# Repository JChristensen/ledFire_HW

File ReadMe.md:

# LED PWM Fire Effect (Hardware Design)#
http://github.com/JChristensen/ledFire_HW  
ReadMe file  
Jack Christensen Dec 2014

## Introduction ##

A small project to simulate the appearance of a candle or other small fire using pulse width modulation and an ATtiny84A microcontroller. The original application of this project was to light a Halloween jack-o-lantern.

[Here](https://vimeo.com/110424346) is a video.  
Firmware is available [on GitHub](http://goo.gl/VueLrD).  
PC boards can be ordered [from OSH Park](https://www.oshpark.com/shared_projects/ASV7G4qa).  
A Bill of Materials with Mouser part numbers is part of this repo.

## Circuit Details ##

The circuit is meant to run on two AA cells; either alkaline or rechargeable types (NiMH, NiCd) will work. Battery life with two fresh alkaline cells is over 50 hours continuous with three LEDs installed on the board. The board is sized to fit on the back of a Keystone no. 2462 battery holder.

I use high-brightness LEDs with clear lenses. I only populate three LEDs, two yellow and one red. This worked well for my application. Adding the fourth LED will reduce battery life somewhat but the MCU has four PWM outputs so it is there as an option (the firmware drives all four).

The circuit uses a boost regulator to keep the supply voltage and therefore the LED brightness constant as the battery ages. By default, the regulator supplies 3.3V, but this can be changed to 5V via a solder jumper.

The MCU monitors the supply voltage and once the battery has been exhausted to the point where the regulator cannot supply the proper voltage, the MCU shuts down the circuit and goes into low-power sleep mode. The MCP1640 boost regulator has the ability to operate with less than one volt input; this can drain the battery to the point where the cells leak, so the shutdown mechanism is implemented in an effort to prevent this.

The cutoff voltage for the shutdown is selected by another solder jumper; the board is strapped for a 3V cutoff by default (to correspond to the regulator being set for 3.3V). If the regulator is changed to 5V, the cutoff should be changed to 4.5V using the jumper. Having said that, I see little use for operating the circuit with a 5V supply voltage as it will reduce battery life, but it was easy enough to implement at no extra cost (well, one resistor). A 5V supply will also likely require different values for the LED current-limiting resistors.

## CC BY-SA ##
"LED PWM Fire Effect" by Jack Christensen is licensed under [CC BY-SA 4.0](http://creativecommons.org/licenses/by-sa/4.0/).

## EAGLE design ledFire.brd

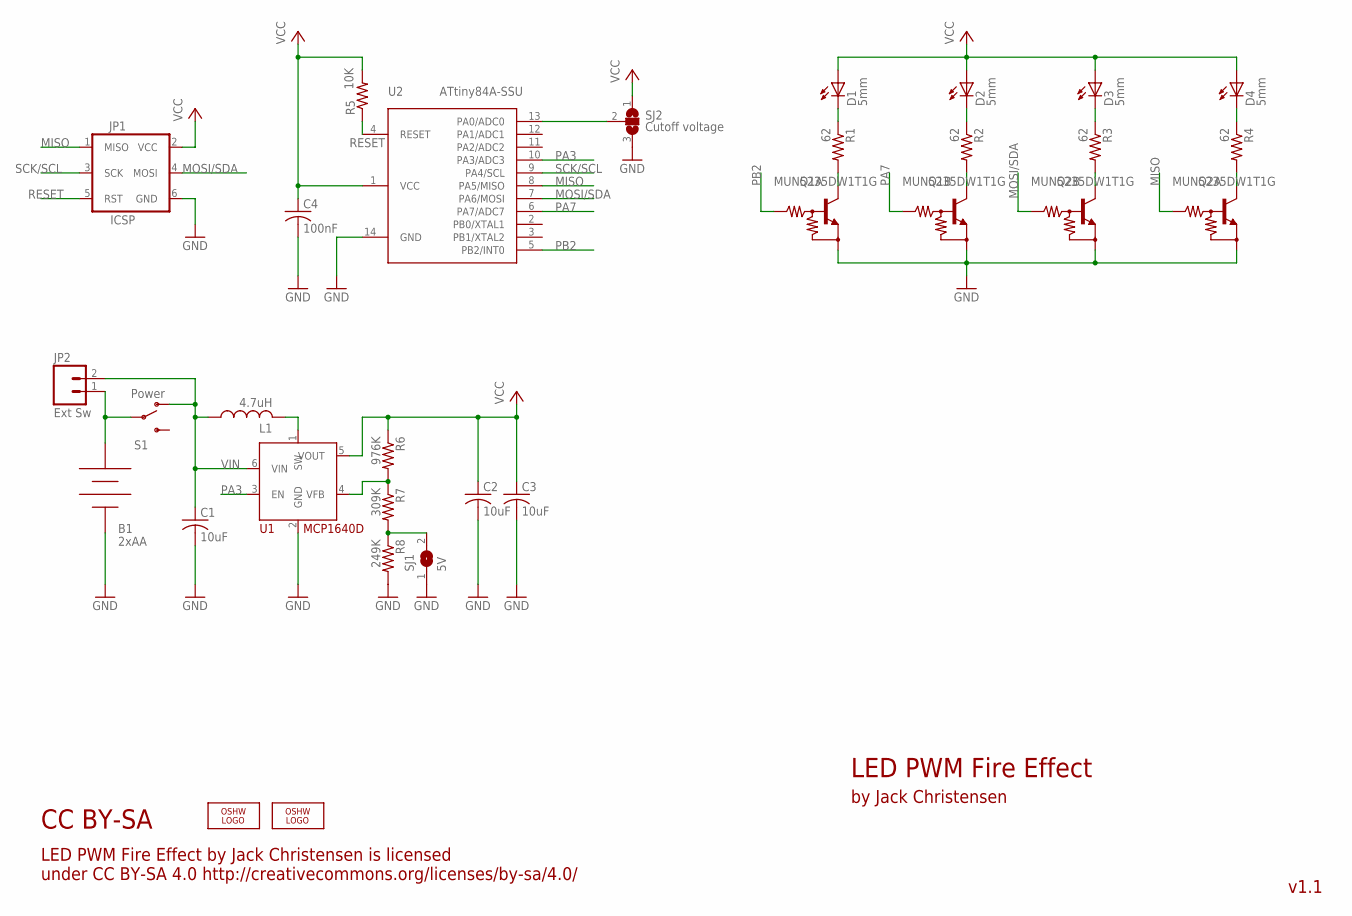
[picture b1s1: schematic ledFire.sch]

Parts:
B1: 2xAA; KEYSTONE-2462-NO-HOLES
C1, C2, C3: 10uF; M0805
C4: 100nF; M0805
D1, D2, D3, D4: 5mm; LED5MM
JP1: ICSP; 2X3_LOCK
JP2: Ext Sw; 1X02_LONGPADS
L1: 4.7uH; NRS5020
LOGO1, LOGO2: OSHW_LOGO_8MILX0100-NT; OSHW_8X100_NOTEXT
Q1, Q2: MUN5235DW1T1G; SOT363_PHILIPS
R1, R2, R3, R4: 62; M0805
R5: 10K; M0805
R6: 976K; M0805
R7: 309K; M0805
R8: 249K; M0805
S1: Power; SWITCH-SPDT-SMD
SJ1: 5V; SJ
SJ2: Cutoff voltage; SJ_2
U1: MCP1640D; SOT23-6
U2: ATtiny84A-SSU; SO14

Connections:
GND: B1.NEG, C1.2, C2.2, C3.2, C4.2, JP1.6 (GND), Q1.1 (E), Q1.4 (E), Q2.1 (E), Q2.4 (E), R8.2, SJ1.1, SJ2.3, U1.2 (GND), U2.14 (GND)
MISO: JP1.1 (MISO), Q2.5 (B), U2.8 (PA5/MISO)
MOSI/SDA: JP1.4 (MOSI), Q2.2 (B), U2.7 (PA6/MOSI)
unnamed: D1.K (C), R1.1
unnamed: R6.2, R7.1, U1.4 (VFB)
unnamed: D2.K (C), R2.1
unnamed: Q2.6 (C), R3.2
unnamed: Q1.3 (C), R1.2
unnamed: R7.2, R8.1, SJ1.2
unnamed: L1.P$2 (2), U1.1 (SW)
unnamed: Q1.6 (C), R2.2
unnamed: Q2.3 (C), R4.2
unnamed: B1.POS, JP2.1, S1.2
unnamed: SJ2.2, U2.13 (PA0/ADC0)
unnamed: D4.K (C), R4.1
unnamed: D3.K (C), R3.1
PA3: U1.3 (EN), U2.10 (PA3/ADC3)
PA7: Q1.2 (B), U2.6 (PA7/ADC7)
PB2: Q1.5 (B), U2.5 (PB2/INT0)
RESET: JP1.5 (RST), R5.1, U2.4 (RESET)
SCK/SCL: JP1.3 (SCK), U2.9 (PA4/SCL)
VCC: C2.1, C3.1, C4.1, D1.A, D2.A, D3.A, D4.A, JP1.2 (VCC), R5.2, R6.1, SJ2.1, U1.5 (VOUT), U2.1 (VCC)
VIN: C1.1, JP2.2, L1.P$1 (1), S1.1 (O), U1.6 (VIN)

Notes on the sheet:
LED PWM Fire Effect
by Jack Christensen
LED PWM Fire Effect by Jack Christensen is licensed under CC BY-SA 4.0 http://creativecommons.org/licenses/by-sa/4.0/
CC BY-SA
v1.1

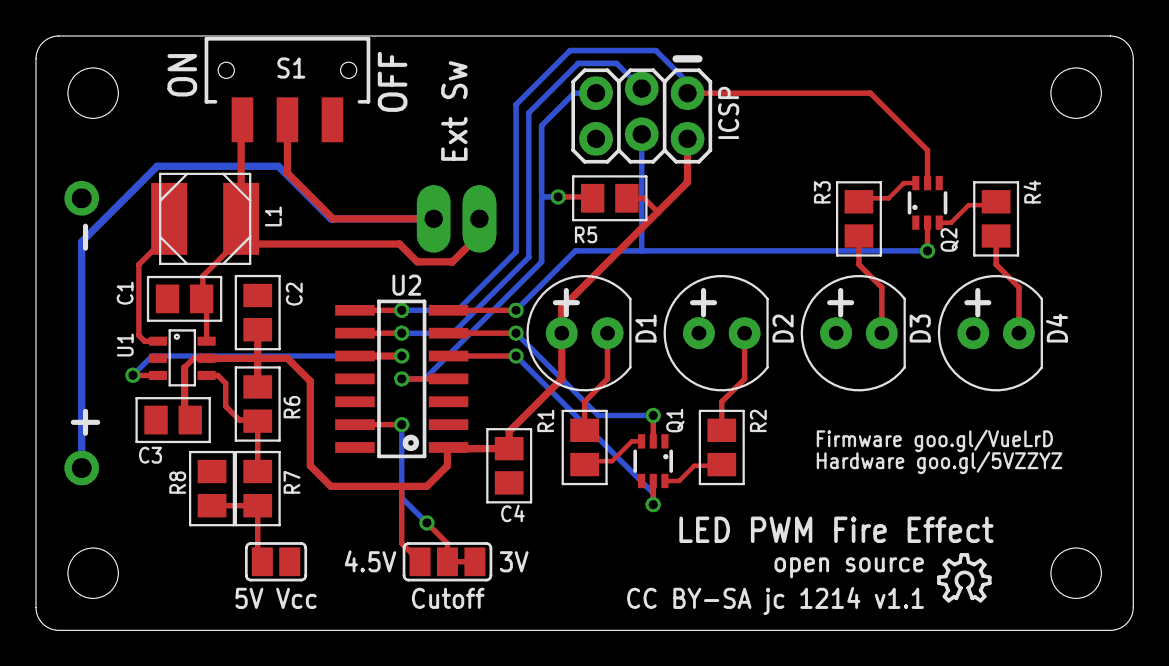
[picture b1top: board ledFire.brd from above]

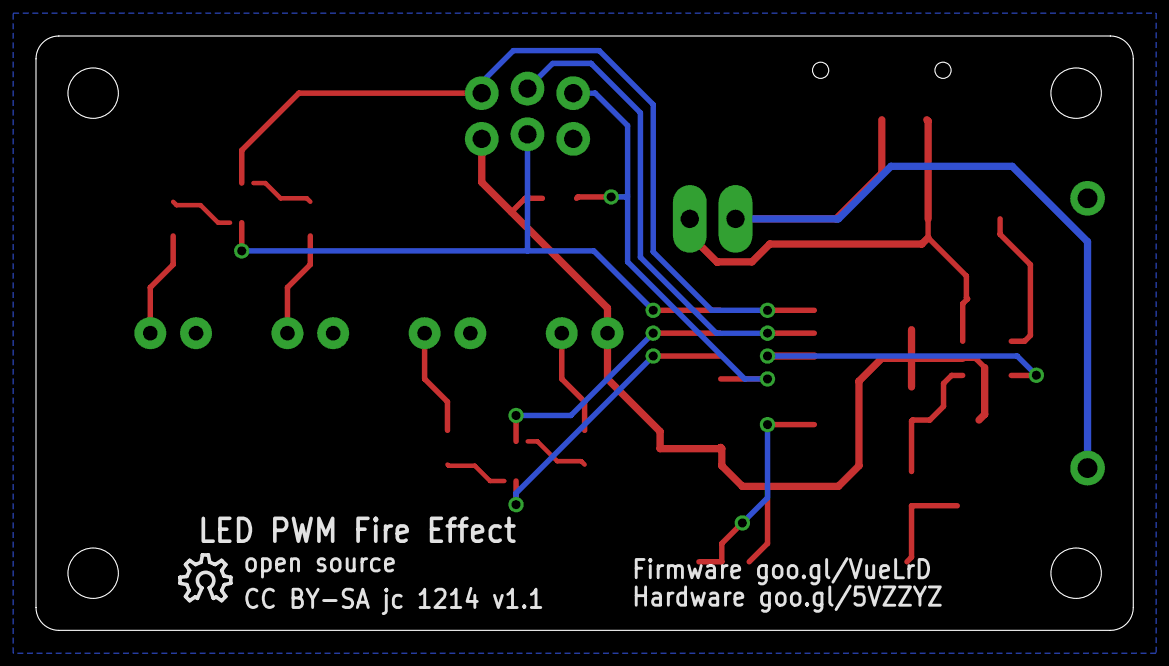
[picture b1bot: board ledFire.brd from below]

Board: 2 copper layers, 61.0 x 33.0 mm, 29 parts (2 on the bottom side), 23 nets.

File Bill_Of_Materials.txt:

LED PWM Fire Effect
Bill of Materials
Jack Christensen Dec 2014

Part    Value            Package             Mouser Part No.
B1      2xAA             Keystone 2462       534-2462
C1      10uF             M0805               81-GRM21BR71A106KA3L
C2      10uF             M0805               81-GRM21BR71A106KA3L
C3      10uF             M0805               81-GRM21BR71A106KA3L
C4      100nF            M0805               581-08055C104K
D1      Yellow           LED5MM              859-LTL2H3PYK14
D2      Red              LED5MM              859-LTL2H3EZ1K
D3      Yellow           LED5MM              859-LTL2H3PYK14
D4      DNP              LED5MM              (Do Not Populate)
JP1     ICSP                                 (Common Headers)
JP2     Ext Sw                               (Optional External Switch)
L1      4.7uH            4mm x 4mm           963-NRS4018T4R7MDGJ
Q1      MUN5235DW1T1G    SOT363              863-MUN5235DW1T1G
Q2      MUN5235DW1T1G    SOT363              863-MUN5235DW1T1G
R1      62               M0805               660-RK73H2ATTD62R0F
R2      62               M0805               660-RK73H2ATTD62R0F
R3      62               M0805               660-RK73H2ATTD62R0F
R4      62               M0805               660-RK73H2ATTD62R0F
R5      10K              M0805               660-RK73H2ATTD1002F
R6      976K             M0805               660-RK73H2ATTD9763F
R7      309K             M0805               660-RK73H2ATTD3093F
R8      249K             M0805               660-RK73H2ATTD2493F
S1      Power            C&K JS102011SAQN    611-JS102011SAQN
SJ1     5V               Solder Jumper       (N/A)
SJ2     Cutoff voltage   Solder Jumper       (N/A)
U1      MCP1640D         SOT23-6             579-MCP1640DT-I/CHY
U2      ATtiny84A-SSU    SO14                556-ATTINY84A-SSU

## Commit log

2014-11-22 Initial commit.
2014-11-22 Add License, ReadMe files.
2014-12-23 v1.1, board corrections.
2014-12-23 Update board and schematic images.
2014-12-23 Update part list.
2014-12-24 Tweak SOT363 footprint.
2014-12-24 Tweak switch footprint.
2014-12-28 Minor adjustments to a couple labels and one trace.
2014-12-28 Update schematic and board images.
2014-12-28 Update ReadMe file and partList.
2014-12-29 Add Bill of Materials.
2014-12-29 Update ReadMe file.
2014-12-29 Add photos.
2015-01-03 Modified SOT-363 footprint, again. Update comment re battery life.

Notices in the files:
ledFire.brd:
CC BY-SA jc 1214 v1.1
parts and their libraries:
SparkFun: Licensing: CC v3.0 Share-Alike You are welcome to use this library for commercial purposes.
